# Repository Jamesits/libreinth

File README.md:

# libreinth

Libreinth (reads: /ˈlibəɹɪnθ/) is a collection of TPM daughter boards compatible with some motherboards with TPM/LPC headers.

Notes:

- They are not tested and might fry your computer; use it at your own risk
- Every board comes with its own caveats; please read the board's readme before using

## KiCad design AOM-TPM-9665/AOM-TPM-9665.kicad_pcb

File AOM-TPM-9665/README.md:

Notes:

- Not every resistor should be soldered; solder R2, R3, R9, R16 for the official configuration
- The 3-pin connector on the side can be used as a physical presense pin; you need to adjust the resistors to achieve this

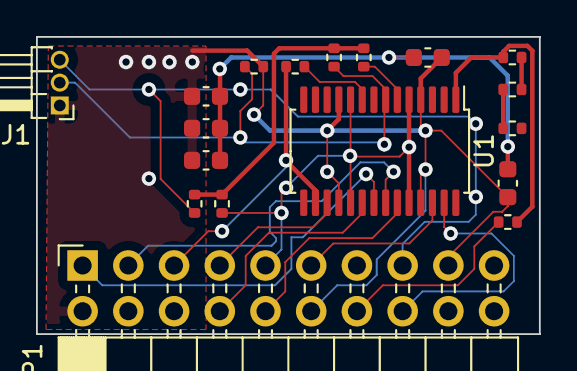
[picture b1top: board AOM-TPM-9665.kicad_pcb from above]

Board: 2 copper layers, 27.9 x 16.5 mm, 18 parts (0 on the bottom side), 20 nets.

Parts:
C1, C2, C3, C4: 100n; C_0603_1608Metric
C5: 1u; C_0603_1608Metric
J1: Conn_01x03; PinHeader_1x03_P1.27mm_Horizontal
JP1: Conn_02x10_Odd_Even; PinSocket_2x10_P2.54mm_Horizontal
R2, R16, R17: 0; R_0402_1005Metric
R3, R4, R5, R6, R7, R8, R9: R; R_0402_1005Metric
U1: SLB9665xT; TSSOP-28_4.4x9.7mm_P0.65mm

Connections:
+3.3VP: J1.3, JP1.15, R17.2
+3V3: JP1.9, R16.2, U1.5, U1.10, U1.19, U1.24
GND: C1.2, C2.2, C3.2, C4.2, C5.2, J1.1, JP1.2, JP1.12, JP1.17, R3.1, U1.4, U1.11, U1.18, U1.25
GPIO: R9.1, U1.6
LAD0: JP1.11, U1.26
LAD1: JP1.10, U1.23
LAD2: JP1.8, U1.20
LAD3: JP1.7, U1.17
LCLK: JP1.1, U1.21
LFRAME#: JP1.3, U1.22
LRESET#: JP1.5, R2.1, U1.16
unnamed: C1.1, C2.1, C3.1, C4.1, C5.1
unnamed: R4.1, R7.2
unnamed: R6.2, R7.1
P1: R5.1, R6.1, U1.1
PP: J1.2, R3.2, R8.1, U1.7
PWR: R8.2, R9.2, R16.1, R17.1
RESET: R2.2, U1.9
SERIRQ: JP1.16, U1.27
SMB_DAT: JP1.14, R5.2

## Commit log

2021-10-10 add license
